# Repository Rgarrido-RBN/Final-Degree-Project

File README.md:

# Final-Degree-Project
# Final-Degree-Project

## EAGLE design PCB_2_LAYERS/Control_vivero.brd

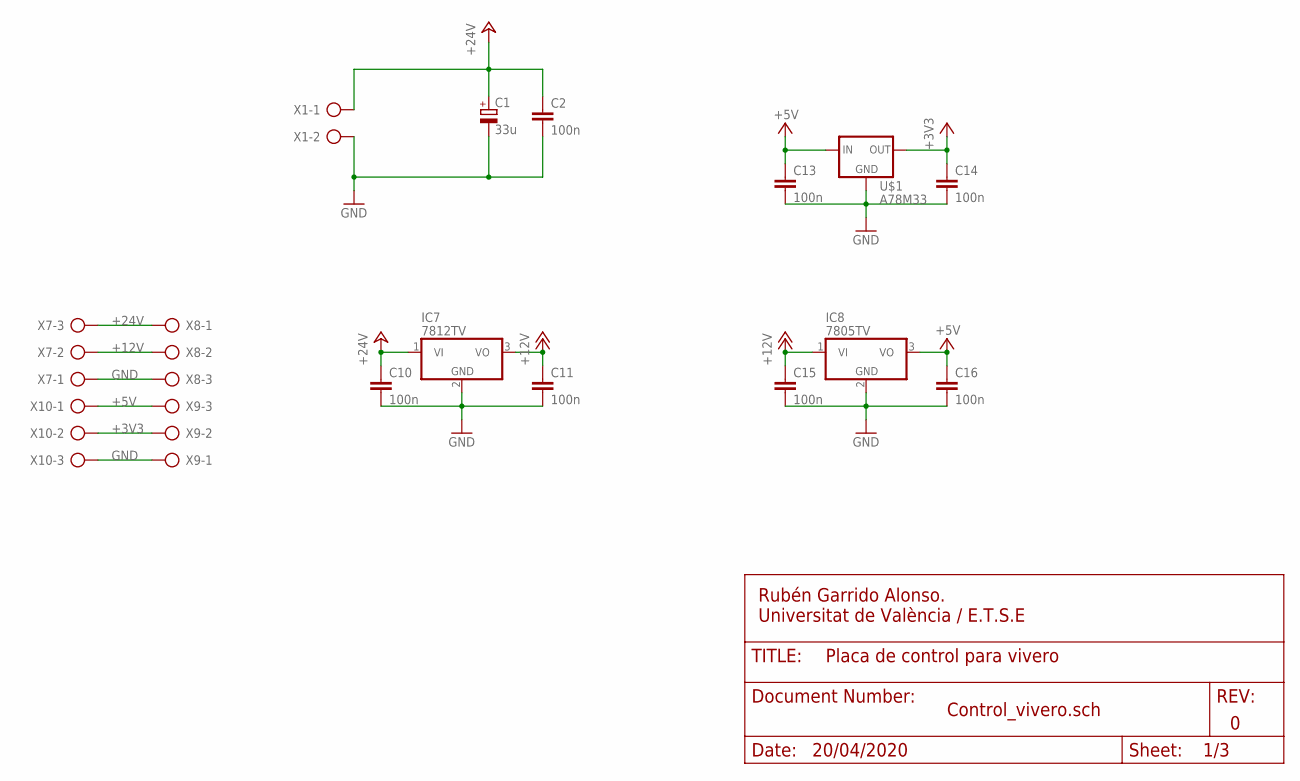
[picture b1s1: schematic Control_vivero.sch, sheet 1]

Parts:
C1: 33u; E2,5-7
C2, C10, C11, C13, C14, C15, C16: 100n; C050-025X075
IC7: 7812TV; TO220V
IC8: 7805TV; TO220V
U$1: A78M33; TO-252
X1: AK500/2-H
X7, X8, X9, X10: AK300/3

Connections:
+3V3: C14.1, U$1.OUT, X9.2, X10.2; also elsewhere on the board
+5V: C13.1, C16.1, IC8.3 (VO), U$1.IN, X9.3, X10.1; also elsewhere on the board
+12V: C11.1, C15.1, IC7.3 (VO), IC8.1 (VI), X7.2, X8.2; also elsewhere on the board
+24V: C1.+, C2.1, C10.1, IC7.1 (VI), X1.1, X7.3, X8.1; also elsewhere on the board
GND: C1.-, C2.2, C10.2, C11.2, C13.2, C14.2, C15.2, C16.2, IC7.2 (GND), IC8.2 (GND), U$1.COM (GND), X1.2, X7.1, X8.3, X9.1, X10.3; also elsewhere on the board

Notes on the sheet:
Rubén Garrido Alonso. Universitat de València / E.T.S.E
Placa de control para vivero
Control_vivero.sch
20/04/2020

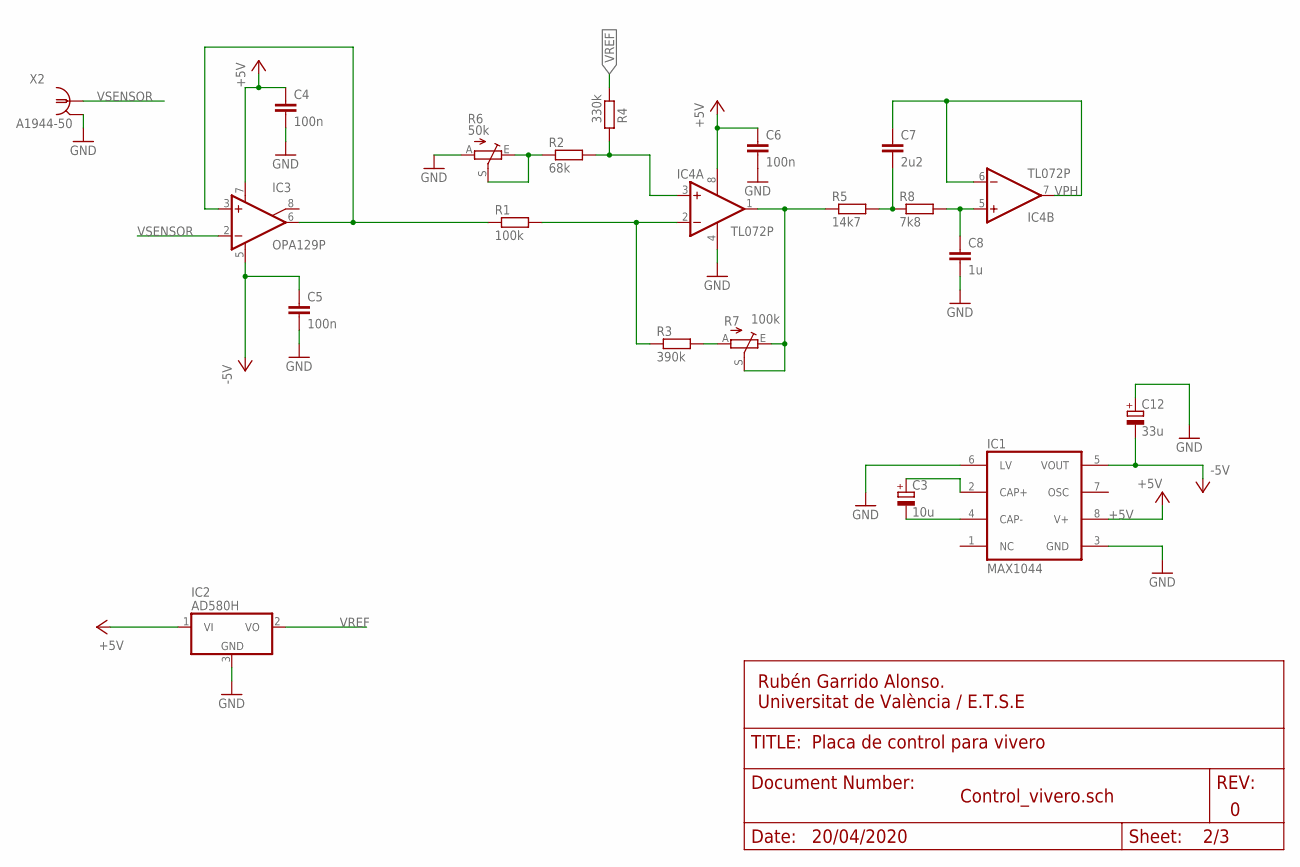
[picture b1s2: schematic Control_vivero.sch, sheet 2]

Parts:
C3: 10u; E2,5-6E
C4, C5, C6: 100n; C050-025X075
C7: 2u2; C050-055X075
C8: 1u; C050-055X075
C12: 33u; E2,5-6E
IC1: MAX1044; DIL08
IC2: AD580H; TO39
IC3: OPA129P; DIL08
IC4: TL072P; DIL08
R1: 100k; 0207/10
R2: 68k; 0207/10
R3: 390k; 0207/10
R4: 330k; 0207/10
R5: 14k7; 0207/10
R6: 50k; B25P
R7: 100k; B25P
R8: 7k8; 0207/10
X2: A1944-50; A1944

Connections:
+5V: C4.1, C6.1, IC1.8 (V+), IC2.1 (VI), IC3.7 (V+), IC4.8 (V+); also elsewhere on the board
-5V: C5.1, C12.-, IC1.5 (VOUT), IC3.5 (V-)
GND: C4.2, C5.2, C6.2, C8.2, C12.+, IC1.3 (GND), IC1.6 (LV), IC2.3 (GND), IC4.4 (V-), R6.A, X2.2, X2.3 (2), X2.4 (2), X2.5 (2); also elsewhere on the board
unnamed: C3.+, IC1.2 (CAP+)
unnamed: C3.-, IC1.4 (CAP-)
unnamed: R3.2, R7.A
unnamed: IC3.3 (+IN), IC3.6 (OUT), R1.1
unnamed: IC4.1 (OUT), R5.1, R7.E, R7.S
unnamed: IC4.3 (+IN), R2.2, R4.2
unnamed: R2.1, R6.E, R6.S
unnamed: C7.2, R5.2, R8.1
unnamed: C8.1, IC4.5 (+IN), R8.2
unnamed: IC4.2 (-IN), R1.2, R3.1
VPH: C7.1, IC4.6 (-IN), IC4.7 (OUT); also elsewhere on the board
VREF: IC2.2 (VO), R4.1
VSENSOR: IC3.2 (-IN), X2.1

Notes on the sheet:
Rubén Garrido Alonso. Universitat de València / E.T.S.E
Placa de control para vivero
Control_vivero.sch
20/04/2020

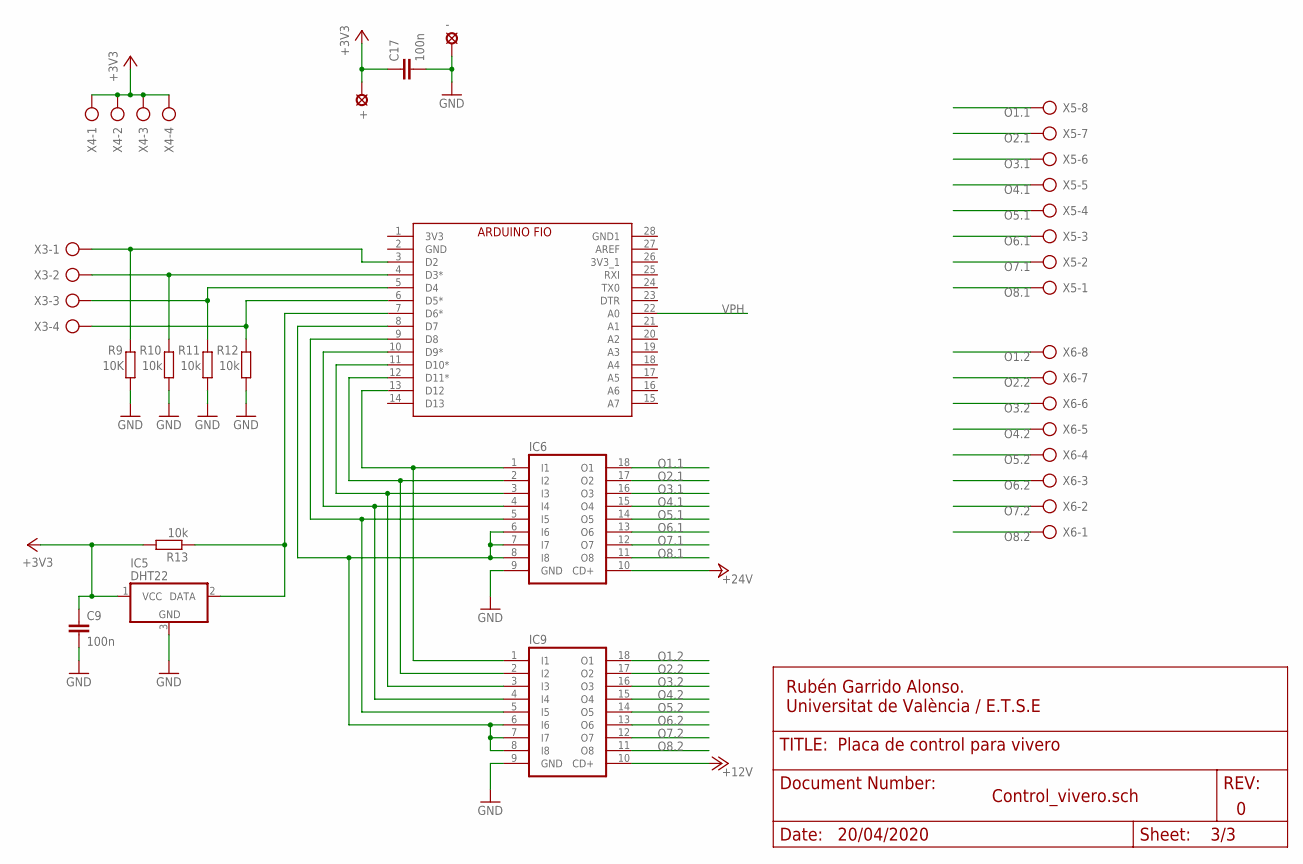
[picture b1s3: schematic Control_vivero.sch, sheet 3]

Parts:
+: LSP10
-: LSP10
B1: ARDUINO_FIO; ARDUINO_FIO_SOCKET
C9, C17: 100n; C050-025X075
IC5: DHT22; AK300/3
IC6, IC9: ULN2803A; DIL18
R9: 10K; 0207/10
R10, R11, R12, R13: 10k; 0207/10
X3, X4: AK300/4
X5, X6: AK300/8

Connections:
+3V3: +.MP, C9.1, C17.1, IC5.1 (VCC), R13.2, X4.1, X4.2, X4.3, X4.4; also elsewhere on the board
+12V: IC9.10 (CD+); also elsewhere on the board
+24V: IC6.10 (CD+); also elsewhere on the board
GND: -.MP, C9.2, C17.2, IC5.3 (GND), IC6.9 (GND), IC9.9 (GND), R9.1, R10.1, R11.1, R12.1; also elsewhere on the board
unnamed: B1.3 (D2), R9.2, X3.1
unnamed: B1.4 (D3*), R10.2, X3.2
unnamed: B1.5 (D4), R11.2, X3.3
unnamed: B1.6 (D5*), R12.2, X3.4
unnamed: B1.7 (D6*), IC5.2 (DATA), R13.1
unnamed: B1.8 (D7), IC6.6 (I6), IC6.7 (I7), IC6.8 (I8), IC9.6 (I6), IC9.7 (I7), IC9.8 (I8)
unnamed: B1.10 (D9*), IC6.4 (I4), IC9.4 (I4)
unnamed: B1.9 (D8), IC6.5 (I5), IC9.5 (I5)
unnamed: B1.11 (D10*), IC6.3 (I3), IC9.3 (I3)
unnamed: B1.12 (D11*), IC6.2 (I2), IC9.2 (I2)
unnamed: B1.13 (D12), IC6.1 (I1), IC9.1 (I1)
O1.1: IC6.18 (O1), X5.8
O1.2: IC9.18 (O1), X6.8
O2.1: IC6.17 (O2), X5.7
O2.2: IC9.17 (O2), X6.7
O3.1: IC6.16 (O3), X5.6
O3.2: IC9.16 (O3), X6.6
O4.1: IC6.15 (O4), X5.5
O4.2: IC9.15 (O4), X6.5
O5.1: IC6.14 (O5), X5.4
O5.2: IC9.14 (O5), X6.4
O6.1: IC6.13 (O6), X5.3
O6.2: IC9.13 (O6), X6.3
O7.1: IC6.12 (O7), X5.2
O7.2: IC9.12 (O7), X6.2
O8.1: IC6.11 (O8), X5.1
O8.2: IC9.11 (O8), X6.1
VPH: B1.22 (A0); also elsewhere on the board

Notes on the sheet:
Rubén Garrido Alonso. Universitat de València / E.T.S.E
Placa de control para vivero
Control_vivero.sch
20/04/2020

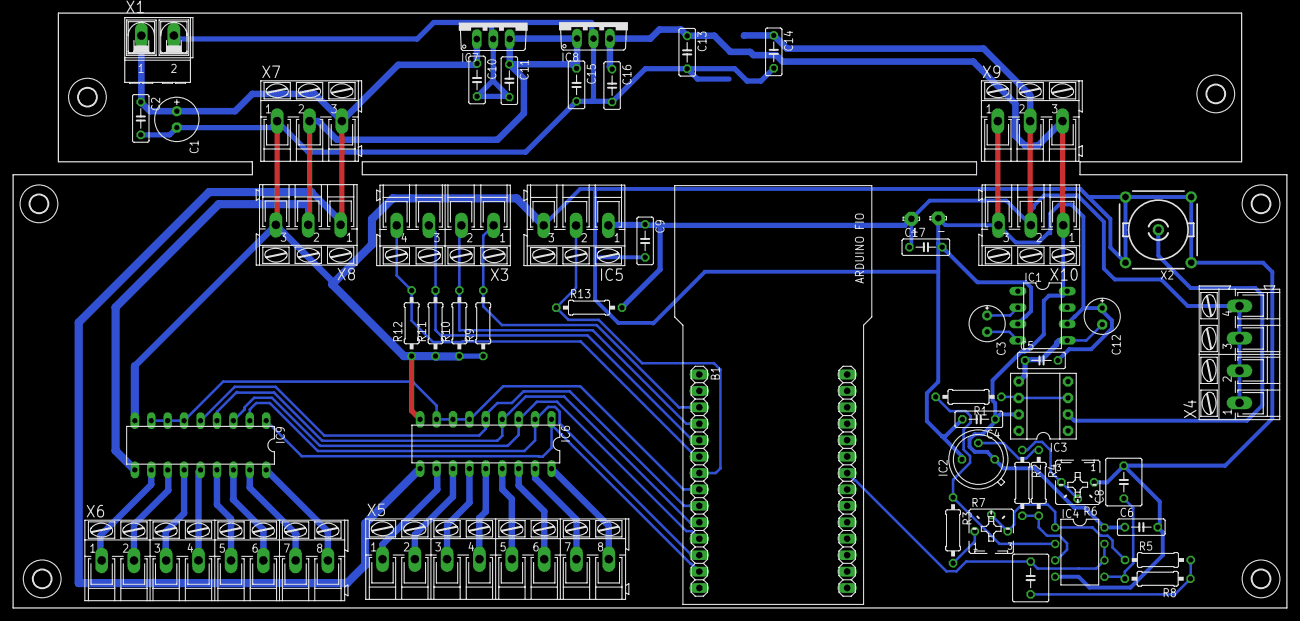
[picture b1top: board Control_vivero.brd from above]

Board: 2 copper layers, 197.0 x 92.0 mm, 59 parts (1 on the bottom side), 46 nets.

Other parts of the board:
U$2, U$3, U$4, U$5, U$6, U$7: 2,8

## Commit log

2021-01-15 my final degree project
